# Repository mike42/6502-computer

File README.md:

# 6502 computer

This repository contains the hardware and software for my home-built 65C02-based computer. At its heart, this computer is a 1980's design, and is approximately as powerful as the Apple II. It is powered over USB, and operated via a serial connection.

It features an SD card interface, simple audio interface, and two user-selectable ROMs. One ROM contains a port of EhBASIC, which is the only proprietary component in this repository. The other ROM contains a shell, written from scratch to be free and open source, which can be used to load machine-language programs from a modern PC.

Take a look at the [hardware/](https://github.com/mike42/6502-computer/tree/main/hardware) directory for how it's made, or [rom/](https://github.com/mike42/6502-computer/tree/main/rom) for the firmware source code.

### Basic specs

- 1.8432 MHz 65C02 processor
- 32 KiB RAM
- 32 KiB ROM in two 16 KiB banks
- 65C22 VIA (general purpose I/O) chip
- 65C51N ACIA (UART) interface
- Custom PCB and 3D printed case

### Image of completed build

## Blog series

This project started out on breadboards, and I have been blogging about it as I have progressed the hardware, software, and my electronics knowlege. Posts I've written about this project include:

- [IntelliJ plugin for 6502 assembly language](https://mike42.me/blog/2021-05-intellij-plugin-for-6502-assembly-language)
- [Building a 6502 computer](https://mike42.me/blog/2021-07-building-a-6502-computer)
- [Adding a serial port to my 6502 computer](https://mike42.me/blog/2021-07-adding-a-serial-port-to-my-6502-computer)
- [Upgrades and improvements to my 6502 computer](https://mike42.me/blog/2021-08-upgrades-and-improvements-to-my-6502-computer)
- [Porting BASIC to my 6502 computer](https://mike42.me/blog/2021-09-porting-basic-to-my-6502-computer)
- [6502 computer – from breadboard to PCB](https://mike42.me/blog/2021-09-6502-computer-from-breadboard-to-pcb)
- [Re-creating the world’s worst sound card](https://mike42.me/blog/2021-10-re-creating-the-worlds-worst-sound-card)
- [Designing a 3D printed enclosure for my KiCad project in Blender](https://mike42.me/blog/2021-11-designing-a-3d-printed-enclosure-for-my-kicad-project-in-blender)
- [Implementing the XMODEM protocol for file transfer](https://mike42.me/blog/2021-12-implementing-the-xmodem-protocol-for-file-transfer)
- [Adding an SD card reader to my 6502 computer](https://mike42.me/blog/2021-12-adding-an-sd-card-reader-to-my-6502-computer)
- [Assembling my 6502 computer](https://mike42.me/blog/2012-12-assembling-my-6502-computer)
- [Rendering my 6502 computer project in Blender](https://mike42.me/blog/2022-01-rendering-my-6502-computer-project-in-blender)

## Licenses & acknowledgement

With the exception of the files noted below, this work is © 2021 Michael Billington, and is licensed under a [Creative Commons Attribution 4.0 International License](http://creativecommons.org/licenses/by/4.0/).

The design is an extension of [Ben Eater's 6502 computer tutorial](https://eater.net/6502), which is itself based on the work of the [6502.org](http://www.6502.org/) community.

### 6502 KiCad Library

The files `hardware/kicad/65xx.dcm` and `hardware/kicad/65xx.lib` are modified versions of the [6502 KiCad Library](https://github.com/Alarm-Siren/6502-kicad-library). Copyright 2018, Nicholas Parks Young. All Rights Reserved. The 6502 KiCad Library library is licensed under the GNU LGPL v2.1, which can be found in file `licenses/LGPL.txt`.

### EhBASIC

The files in `rom/basic/` are derived from EhBASIC, developed by Lee Davidson. The EhBASIC license allows for non-commerical use only. The most recent release and manual is hosted [here](https://github.com/Klaus2m5/6502_EhBASIC_V2.22), and a mirror of Lee's website can be found [here](http://retro.hansotten.nl/6502-sbc/lee-davison-web-site/).

> EhBASIC is free but not copyright free. For non commercial use there is only one
> restriction, any derivative work should include, in any binary image distributed,
> the string "Derived from EhBASIC" and in any distribution that includes human
> readable files a file that includes the above string in a human readable form
> e.g. not as a comment in an HTML file.

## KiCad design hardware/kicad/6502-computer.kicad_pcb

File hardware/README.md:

# 6502 computer hardware

This directory contains information about the hardware side of this project.

- [kicad/](https://github.com/mike42/6502-computer/tree/main/hardware/kicad) - CAD source files for schematic and PCB
- [gerber/](https://github.com/mike42/6502-computer/tree/main/hardware/gerber/) - PCB manufacturing files 
- [6502_computer_schematic.pdf](https://github.com/mike42/6502-computer/tree/main/hardware/6502_computer_schematic.pdf) - Human-readable schematic
- [case/](https://github.com/mike42/6502-computer/tree/main/hardware/case/) - STL files for 3D printed computer case.
- Parts list (below)

## Parts list for assembling PCB

This is the full list of parts which are required to fully populate the PCB for this build. I've stuck with the parts which I actually used, though many can be substituted if you check the data sheets.

### IC’s and sockets

Notes on IC's and sockets

- If you see a designator mentioned twice, one is the IC, the other is the socket.
- All sockets are optional except U9.

| Qty. | Description                    | Installed at | Product ref.                                                                         |
| ---- | ------------------------------ | ------------ | ------------------------------------------------------------------------------------ |
|   1  | 65C02S CPU                     | U1           | [WDC W65C02S6TPG-14](https://au.mouser.com/ProductDetail/955-W65C02S6TPG-14)         |
|   1  | 65C22S VIA                     | U3           | [WDC W65C22S6TPG-14](https://au.mouser.com/ProductDetail/955-W65C22S6TPG-14)         |
|   2  | DIP-40 socket                  | U1, U3       | [Mill-Max 110-99-640-41-001000](https://au.mouser.com/ProductDetail/575-199640)      |
|   1  | 65C51N ACIA                    | U6           | [WDC W65C51N6TPG-14](https://au.mouser.com/ProductDetail/955-W65C51N6TPG-14)         |
|   1  | SRAM 32k x 8                   | U8           | [Alliance AS6C62256-55PCN](https://au.mouser.com/ProductDetail/913-AS6C62256-55PCN)  |
|   2  | DIP-28 socket                  | U6, U8       | [Mill-Max 110-99-628-41-001000](https://au.mouser.com/ProductDetail/575-199628)      |
|   1  | EEPROM 32k x 8                 | U9           | [Atmel AT28C256-15PU](https://au.mouser.com/ProductDetail/556-AT28C25615PU)          |
|   1  | Low-profile DIP-28 ZIF socket  | U9           | [Aires 28-526-10](https://au.mouser.com/ProductDetail/535-28-526-10)                 |
|   1  | 74LS138 demultiplexer          | U2           | [Texas Instruments SN74LS138N](https://au.mouser.com/ProductDetail/595-SN74LS138N)   |
|   1  | DIP-16 socket                  | U2           | [Mill-Max 110-44-316-41-001000](https://au.mouser.com/ProductDetail/575-11044316)    |
|   1  | 74LS00 quad NAND gate          | U4           | [Texas Instruments SN74LS00N](https://au.mouser.com/ProductDetail/595-SN74LS00N)     |
|   1  | DIP-14 socket                  | U4           | [Mill-Max 110-44-314-41-001000](https://au.mouser.com/ProductDetail/575-11044314)    |
|   1  | 1.8432 MHz oscillator          | X1           | [CTS MXO45HS-3C-1M8432](https://au.mouser.com/ProductDetail/774-MXO45HS-3C-1.8)      |
|   1  | Oscillator socket              | X1           | [Aires 1108800](https://au.mouser.com/ProductDetail/535-1108800)                     |
|   1  | 7805 voltage regulator         | U5           | [STMicroelectronics L7805ABV](https://au.mouser.com/ProductDetail/511-L7805ABV)      |
|   1  | DS1813 reset / voltage monitor | U7           | [Maxim Integrated DS1813-5+](https://au.mouser.com/ProductDetail/700-DS1813-5%2b)    |

### Connectors

Notes on connectors:

- If you use the exact parts here, then one of the 2x20 headers needs to be snapped apart to populate 2x6 footprints at J4 and J5.
- The shunts at J3 should be installed to connect the VIA to IRQ, and the ACIA to NMI. These are labelled on the PCB.

| Qty. | Description                       | Installed at | Product ref.                                                                                           |
| ---- | --------------------------------- | ------------ | ------------------------------------------------------------------------------------------------------ |
|    2 | 2x20 male pin header              | J1, J4, J5   | [Amphenol FCI 10129381-940002BLF](https://au.mouser.com/ProductDetail/649-1012938194002BLF)            |
|    1 | Barrel jack                       | J2           | [Adafruit 373](https://au.mouser.com/ProductDetail/485-373)                                            |
|    1 | 1x6 male pin header               | J6           | [Amphenol FCI 10129378-906001BLF](https://au.mouser.com/ProductDetail/Amphenol-FCI/10129378-906001BLF) |
|    2 | SPDT switch 2.54mm lead spacing   | SW1, SW2     | [SparkFun COM-00102](https://au.mouser.com/ProductDetail/474-COM-00102)                                |
|    1 | Momentary switch                  | SW3          | [SparkFun COM-00097](https://au.mouser.com/ProductDetail/474-COM-00097)                                |
|    2 | 1x2 male pin header               | J3           | [Amphenol FCI 10129378-902001BLF](https://au.mouser.com/ProductDetail/649-1012937890201BLF)            |
|    2 | Shunt/jumper                      | J3           | [TE Connectivity 2-382811-1](https://au.mouser.com/ProductDetail/571-2-382811-1)                       |

### Basic components

| Qty. | Description                                             | Installed at                         | Product ref.                                                |
| ---- | ------------------------------------------------------- | ------------------------------------ | ----------------------------------------------------------- |
|    1 | 0.1 µF ceramic capacitor, 2.54mm lead spacing (10 pack) | C1, C2, C3, C4, C5, C6, C7, C8, C10  | [Adafruit 753](https://au.mouser.com/ProductDetail/485-753) |
|    1 | 1 µF electrolytic capacitor, 1.5mm lead spacing         | C9                                   | –                                                           |
|    1 | 1N5819 schottky diode                                   | D1                                   | –                                                           |
|    1 | 5.0 mm LED                                              | D2                                   | –                                                           |
|    3 | 3.3 kΩ resistor 1/4w                                    | R1 R2 R4                             | –                                                           |
|    1 | 1 kΩ resistor 1/4w                                      | R3                                   | –                                                           |

## Additional parts to install in case

| Qty. | Description                                              | Product ref.                                                                                                 |
| ---- | -------------------------------------------------------- | ------------------------------------------------------------------------------------------------------------ |
|    1 | 16mm Illuminated Pushbutton - Red Latching On/Off Switch | [Adafruit 1442](https://core-electronics.com.au/16mm-illuminated-pushbutton-red-latching-on-off-switch.html) |
|    1 | 330 Ω resistor 1/4w                                      | –                                                                                                            |
|    1 | Momentary Button - Panel Mount                           | [SparkFun COM-11006](https://core-electronics.com.au/momentary-button-panel-mount-black.html)                |
|    1 | Piezo Buzzer                                             | [TDK PS1240P02BT](https://core-electronics.com.au/piezo-buzzer-ps1240.html)                                  |
|    4 | M3 x 5+6mm hex standoff                                  | Generic, similar to [this](https://www.minikits.com.au/SPA-M3x5-6-B-C)                                       |
|    4 | M3 nut                                                   | [Polulu 1069](https://core-electronics.com.au/machine-hex-nut-m3-25-pack.html)                               |
|    4 | M3 x 5 mm screw                                          | [Polulu 1075](https://core-electronics.com.au/machine-screw-m3-5mm-length-phillips-25-pack.html)             |
|    1 | Heat-shrink tubing kit                                   | [Adafruit 344](https://core-electronics.com.au/heat-shrink-pack.html)                                        |
|    1 | Stranded wire                                            | –                                                                                                            |
|    1 | Du Pont connector kit                                    | –                                                                                                            |
|    1 | FTDI Cable 5V (FT232RQ-based)                            | [Sparkfun DEV-09718](https://core-electronics.com.au/ftdi-cable-5v.html)                                     |
|    1 | Adhesive rubber feet                                     | [Adafruit 550](https://core-electronics.com.au/little-rubber-bumper-feet-pack-of-4.html)                     |

### Case installation notes

First solder three pairs of wires to the underside of the PCB for adding connectors. Each wire is soldered to the PCB on one end, with a female Du Pont connector on the other end (2 x 1 housing).

- Power: Attach to pins 1 and 2 of SW1 to control DC barrel jack, or attach between Pin 4 of J6 (labelled `NC`) and Pin 1 of J5 (labelled `5V`) for power over USB.
- Reset: Connect to underside of SW3. One wire should attach to `GND`, the other to `RES`.
- Speaker: Connect to underside of J1, at pins 24 (labelled `IO2`) and pin 2 (labelled `GND`).

Next, add the corresponding connectors to the power/reset buttons and speaker.

- Power: Solder a wire to each power terminal, and terminate it to a 2x1 male Du Point connector. Solder a wire to each LED terminal, adding a resistor on the GND line, and terminating them to a 2x1 female Du Pont connector.
- Reset: Solder wire to each terminal, terminate to a 2x1 male Du Pont connector
- Speaker: Solder wire to each terminal, terminate to a 2x1 male Du Pont connector

To assemble, first check that the reset button fits (the hole is too small in the case model, and will need to be expanded). Install stand-offs, then feed the UART cable through the oval-shaped hole. Next, add the PCB, and install the power and reset buttons. After this, you can connect the UART cable, power button, and reset button to the board. The power LED connects to pin 1 and 2 of J5. The final step is to super-glue the speaker over the hole at the back of the case.

## Additional parts to install microSD

Some of the test programs in this repository expect an SD card to be connected. Any 5V-compatible microSD break-out board could be used. These exact parts will fit inside the case with the lid closed.

| Qty. | Description                                              | Product ref.                                                                                          |
| ---- | -------------------------------------------------------- | ----------------------------------------------------------------------------------------------------- |
|    1 | Level Shifting microSD Breakout                          | [Sparkfun DEV-13743](https://core-electronics.com.au/sparkfun-level-shifting-microsd-breakout.html)   |
|    1 | 1x7 male pin header                                      | Generic, similar to [this](https://au.mouser.com/ProductDetail/Amphenol-FCI/10129378-907001BLF)       |
|    1 | 1x7 female pin header                                    | [Polulu 1017](https://core-electronics.com.au/0-100-2-54-mm-female-header-1x7-pin-straight.html)      |
|    1 | 2x6 female Du Pont housing                               | [Polulu 1914](https://core-electronics.com.au/0-1-2-54mm-crimp-connector-housing-2x6-pin-5-pack.html) |
|    1 | microSD card 16 GB                                       | –                                                                                                     |

### microSD installation notes

These parts can be used to install a microSD card in the case, attaching to J4. The card sits parallel to J4.

Glue the female pin header to the side of the Du Pont housing to make an adapter. You will need 6 wires, soldered on one end, and with a female Du Pont connector on the other end:

- Pin 1 (labelled `5V`) connects to `VCC`
- Pin 2 (labelled `GND`) connects to `GND`
- Pin 5 (labelled `PA0`) connects to `DO`
- Pin 6 (labelled `PA1`) connects to `SCK`
- Pin 7 (labelled `PA2`) connects to `DI`
- Pin 8 (labelled `PA3`) connects to `CS`

Solder the male pin headers to the microSD breakout, connect the module to the adapter, and attach it to J4. Wiggle it around a bit, and add insulating tape to anything it can contact. You can then fit an SD card.

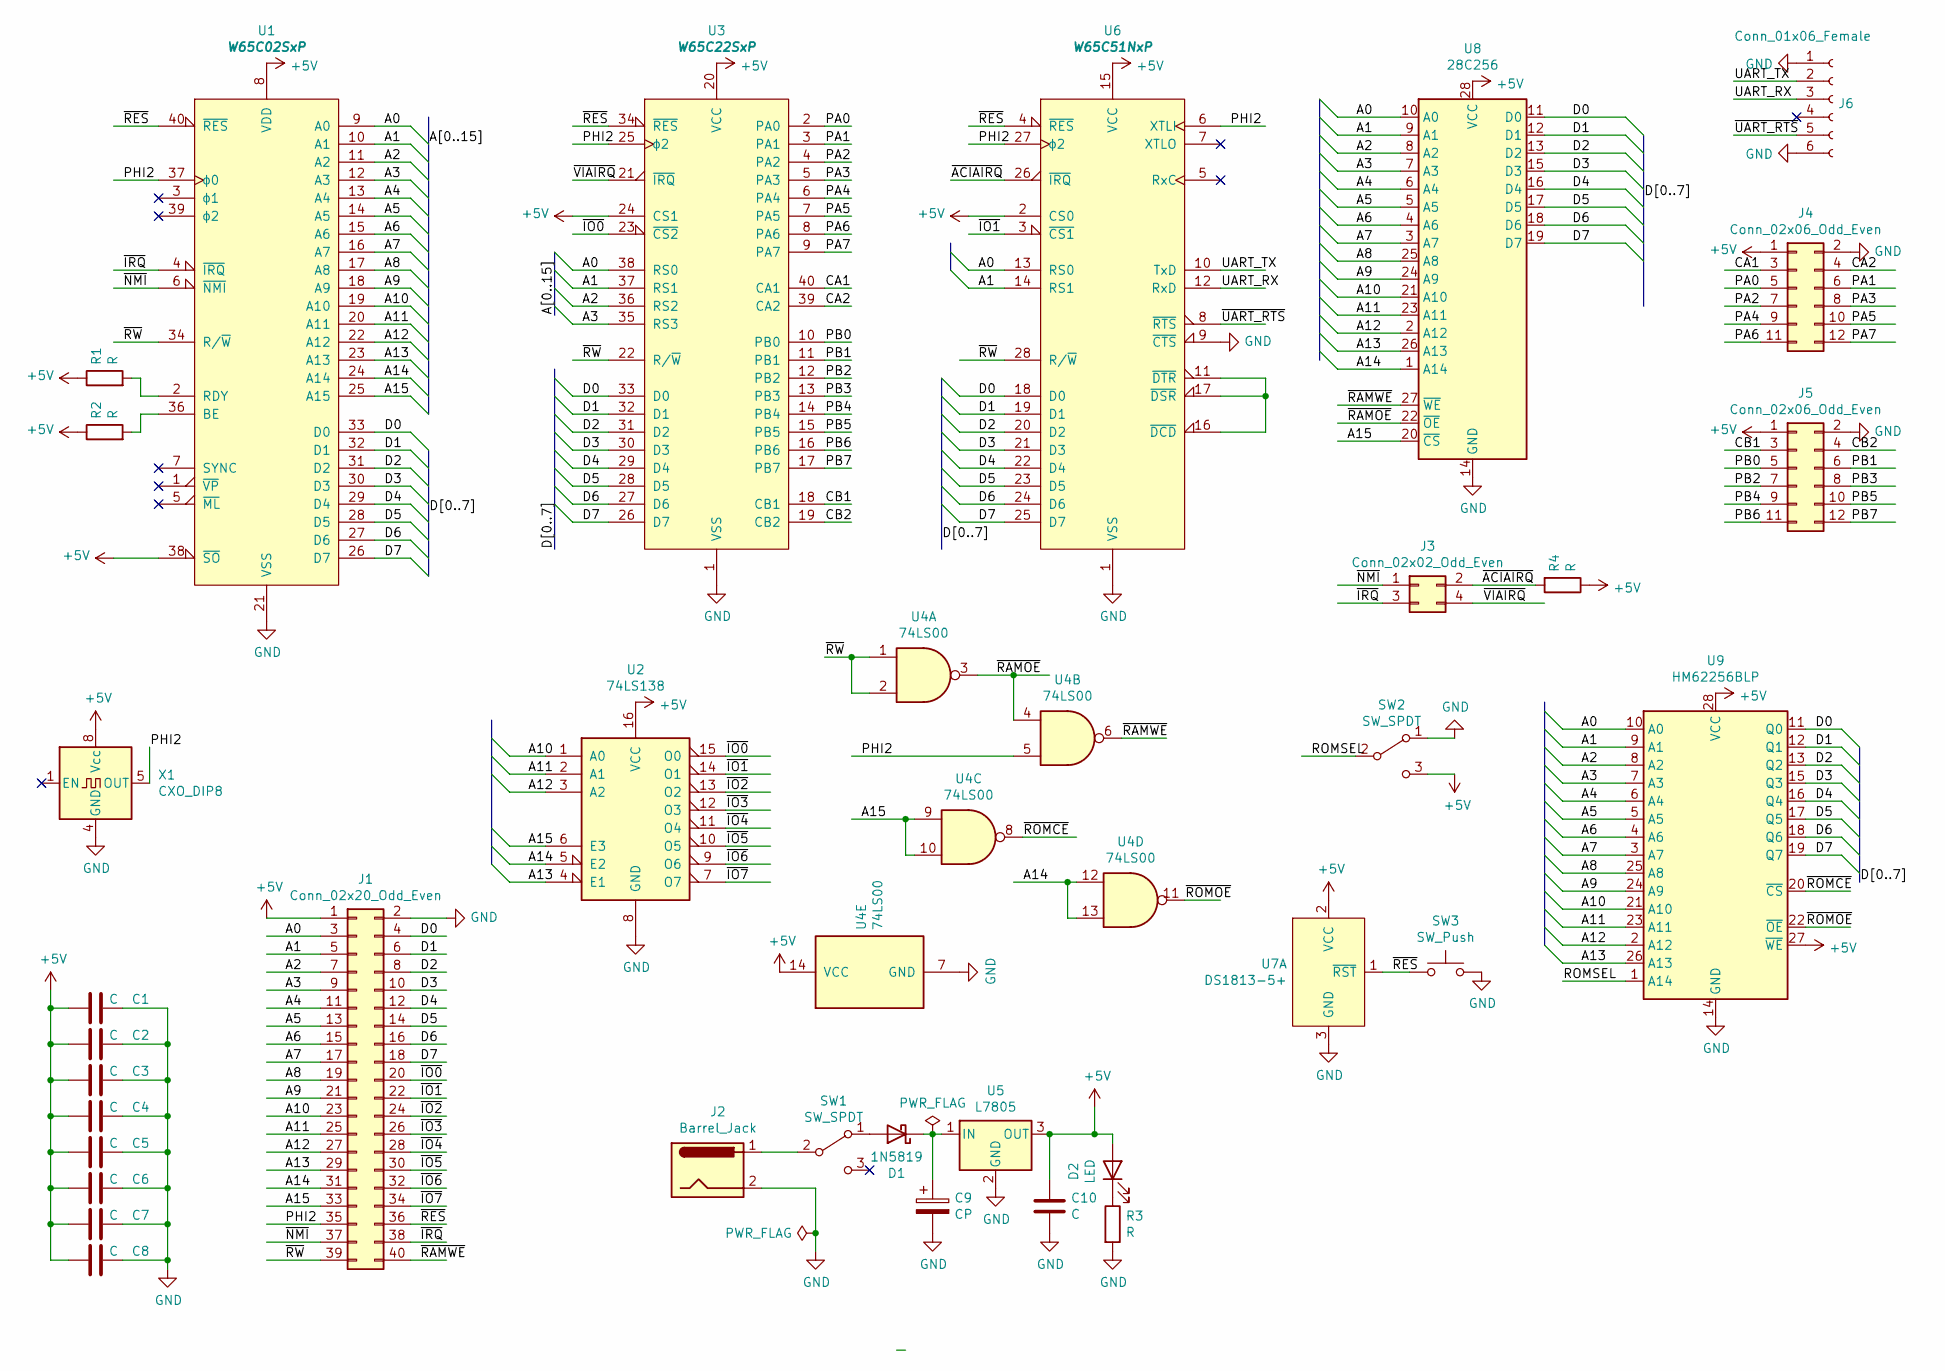
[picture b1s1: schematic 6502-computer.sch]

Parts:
C1, C2, C3, C4, C5, C6, C7, C8, C10: C; C_Disc_D5.0mm_W2.5mm_P2.50mm
C9: CP; C_Radial_D4.0mm_H7.0mm_P1.50mm
D1: 1N5819; D_DO-41_SOD81_P10.16mm_Horizontal
D2: LED; LED_D5.0mm
J1: Conn_02x20_Odd_Even; PinHeader_2x20_P2.54mm_Vertical
J2: Barrel_Jack; BarrelJack_Horizontal
J3: Conn_02x02_Odd_Even; PinHeader_2x02_P2.54mm_Vertical
J4, J5: Conn_02x06_Odd_Even; PinHeader_2x06_P2.54mm_Vertical
J6: Conn_01x06_Female; PinHeader_1x06_P2.54mm_Vertical
R1, R2, R3, R4: R; R_Axial_DIN0207_L6.3mm_D2.5mm_P10.16mm_Horizontal
SW1, SW2: SW_SPDT; SW_THT_DPDT
SW3: SW_Push; SW_Tactile_Straight_KSL0Axx1LFTR
U1: W65C02SxP; DIP-40_W15.24mm_Socket
U2: 74LS138; DIP-16_W7.62mm_Socket
U3: W65C22SxP; DIP-40_W15.24mm_Socket
U4: 74LS00; DIP-14_W7.62mm_Socket
U5: L7805; TO-220-3_Horizontal_TabDown
U6: W65C51NxP; DIP-28_W15.24mm_Socket
U7: DS1813-5+; TO-92
U8: 28C256; DIP-28_W15.24mm_Socket
U9: HM62256BLP; DIP-28_W15.24mm_Socket
X1: CXO_DIP8; Oscillator_DIP-8

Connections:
+5V: C1.2, C2.2, C3.2, C4.2, C5.2, C6.2, C7.2, C8.2, C10.1, D2.2 (A), J1.1, J4.1, J5.1, R1.1, R2.1, R4.1, SW2.3 (C), U1.8 (VDD), U1.38 (~SO), U2.16 (VCC), U3.20 (VCC), U3.24 (CS1), U4.14 (VCC), U5.3 (OUT), U6.2 (CS0), U6.15 (VCC), U7.2 (VCC), U8.28 (VCC), U9.27 (~WE), U9.28 (VCC), X1.8 (Vcc)
/A0: J1.3, U1.9 (A0), U3.38 (RS0), U6.13 (RS0), U8.10 (A0), U9.10 (A0)
/A1: J1.5, U1.10 (A1), U3.37 (RS1), U6.14 (RS1), U8.9 (A1), U9.9 (A1)
/A2: J1.7, U1.11 (A2), U3.36 (RS2), U8.8 (A2), U9.8 (A2)
/A3: J1.9, U1.12 (A3), U3.35 (RS3), U8.7 (A3), U9.7 (A3)
/A4: J1.11, U1.13 (A4), U8.6 (A4), U9.6 (A4)
/A5: J1.13, U1.14 (A5), U8.5 (A5), U9.5 (A5)
/A6: J1.15, U1.15 (A6), U8.4 (A6), U9.4 (A6)
/A7: J1.17, U1.16 (A7), U8.3 (A7), U9.3 (A7)
/A8: J1.19, U1.17 (A8), U8.25 (A8), U9.25 (A8)
/A9: J1.21, U1.18 (A9), U8.24 (A9), U9.24 (A9)
/A10: J1.23, U1.19 (A10), U2.1 (A0), U8.21 (A10), U9.21 (A10)
/A11: J1.25, U1.20 (A11), U2.2 (A1), U8.23 (A11), U9.23 (A11)
/A12: J1.27, U1.22 (A12), U2.3 (A2), U8.2 (A12), U9.2 (A12)
/A13: J1.29, U1.23 (A13), U2.4 (E1), U8.26 (A13), U9.26 (A13)
/A14: J1.31, U1.24 (A14), U2.5 (E2), U4.12, U4.13, U8.1 (A14)
/A15: J1.33, U1.25 (A15), U2.6 (E3), U4.9, U4.10, U8.20 (~CS)
/CA1: J4.3, U3.40 (CA1)
/CA2: J4.4, U3.39 (CA2)
/CB1: J5.3, U3.18 (CB1)
/CB2: J5.4, U3.19 (CB2)
/D0: J1.4, U1.33 (D0), U3.33 (D0), U6.18 (D0), U8.11 (D0), U9.11 (Q0)
/D1: J1.6, U1.32 (D1), U3.32 (D1), U6.19 (D1), U8.12 (D1), U9.12 (Q1)
/D2: J1.8, U1.31 (D2), U3.31 (D2), U6.20 (D2), U8.13 (D2), U9.13 (Q2)
/D3: J1.10, U1.30 (D3), U3.30 (D3), U6.21 (D3), U8.15 (D3), U9.15 (Q3)
/D4: J1.12, U1.29 (D4), U3.29 (D4), U6.22 (D4), U8.16 (D4), U9.16 (Q4)
/D5: J1.14, U1.28 (D5), U3.28 (D5), U6.23 (D5), U8.17 (D5), U9.17 (Q5)
/D6: J1.16, U1.27 (D6), U3.27 (D6), U6.24 (D6), U8.18 (D6), U9.18 (Q6)
/D7: J1.18, U1.26 (D7), U3.26 (D7), U6.25 (D7), U8.19 (D7), U9.19 (Q7)
/PA0: J4.5, U3.2 (PA0)
/PA1: J4.6, U3.3 (PA1)
/PA2: J4.7, U3.4 (PA2)
/PA3: J4.8, U3.5 (PA3)
/PA4: J4.9, U3.6 (PA4)
/PA5: J4.10, U3.7 (PA5)
/PA6: J4.11, U3.8 (PA6)
/PA7: J4.12, U3.9 (PA7)
/PB0: J5.5, U3.10 (PB0)
/PB1: J5.6, U3.11 (PB1)
/PB2: J5.7, U3.12 (PB2)
/PB3: J5.8, U3.13 (PB3)
/PB4: J5.9, U3.14 (PB4)
/PB5: J5.10, U3.15 (PB5)
/PB6: J5.11, U3.16 (PB6)
/PB7: J5.12, U3.17 (PB7)
/PHI2: J1.35, U1.37 (ϕ0), U3.25 (ϕ2), U4.5, U6.6 (XTLI), U6.27 (ϕ2), X1.5 (OUT)
/ROMSEL: SW2.2 (B), U9.1 (A14)
/UART_RX: J6.3, U6.12 (RxD)
/UART_TX: J6.2, U6.10 (TxD)
/~ACIAIRQ: J3.2, R4.2, U6.26 (~IRQ)
/~IO0: J1.20, U2.15 (O0), U3.23 (~CS2)
/~IO1: J1.22, U2.14 (O1), U6.3 (~CS1)
/~IO2: J1.24, U2.13 (O2)
/~IO3: J1.26, U2.12 (O3)
/~IO4: J1.28, U2.11 (O4)
/~IO5: J1.30, U2.10 (O5)
/~IO6: J1.32, U2.9 (O6)
/~IO7: J1.34, U2.7 (O7)
/~IRQ: J1.38, J3.3, U1.4 (~IRQ)
/~NMI: J1.37, J3.1, U1.6 (~NMI)
/~RAMOE: U4.3, U4.4, U8.22 (~OE)
/~RAMWE: J1.40, U4.6, U8.27 (~WE)
/~RES: J1.36, SW3.1, U1.40 (~RES), U3.34 (~RES), U6.4 (~RES), U7.1 (~RST)
/~ROMCE: U4.8, U9.20 (~CS)
/~ROMOE: U4.11, U9.22 (~OE)
/~RW: J1.39, U1.34 (R/~W), U3.22 (R/~W), U4.1, U4.2, U6.28 (R/~W)
/~UART_RTS: J6.5, U6.8 (~RTS)
/~VIAIRQ: J3.4, U3.21 (~IRQ)
GND: C1.1, C2.1, C3.1, C4.1, C5.1, C6.1, C7.1, C8.1, C9.2, C10.2, J1.2, J2.2, J4.2, J5.2, J6.1, J6.6, R3.2, SW2.1 (A), SW3.2, U1.21 (VSS), U2.8 (GND), U3.1 (VSS), U4.7 (GND), U5.2 (GND), U6.1 (VSS), U6.9 (~CTS), U7.3 (GND), U8.14 (GND), U9.14 (GND), X1.4 (GND); also elsewhere on the board
unnamed: C9.1, D1.1 (K), U5.1 (IN)
unnamed: D1.2 (A), SW1.1 (A)
unnamed: D2.1 (K), R3.1
unnamed: J2.1, SW1.2 (B)
unnamed: R1.2, U1.2 (RDY)
unnamed: R2.2, U1.36 (BE)
unnamed: U6.11 (~DTR), U6.16 (~DCD), U6.17 (~DSR)

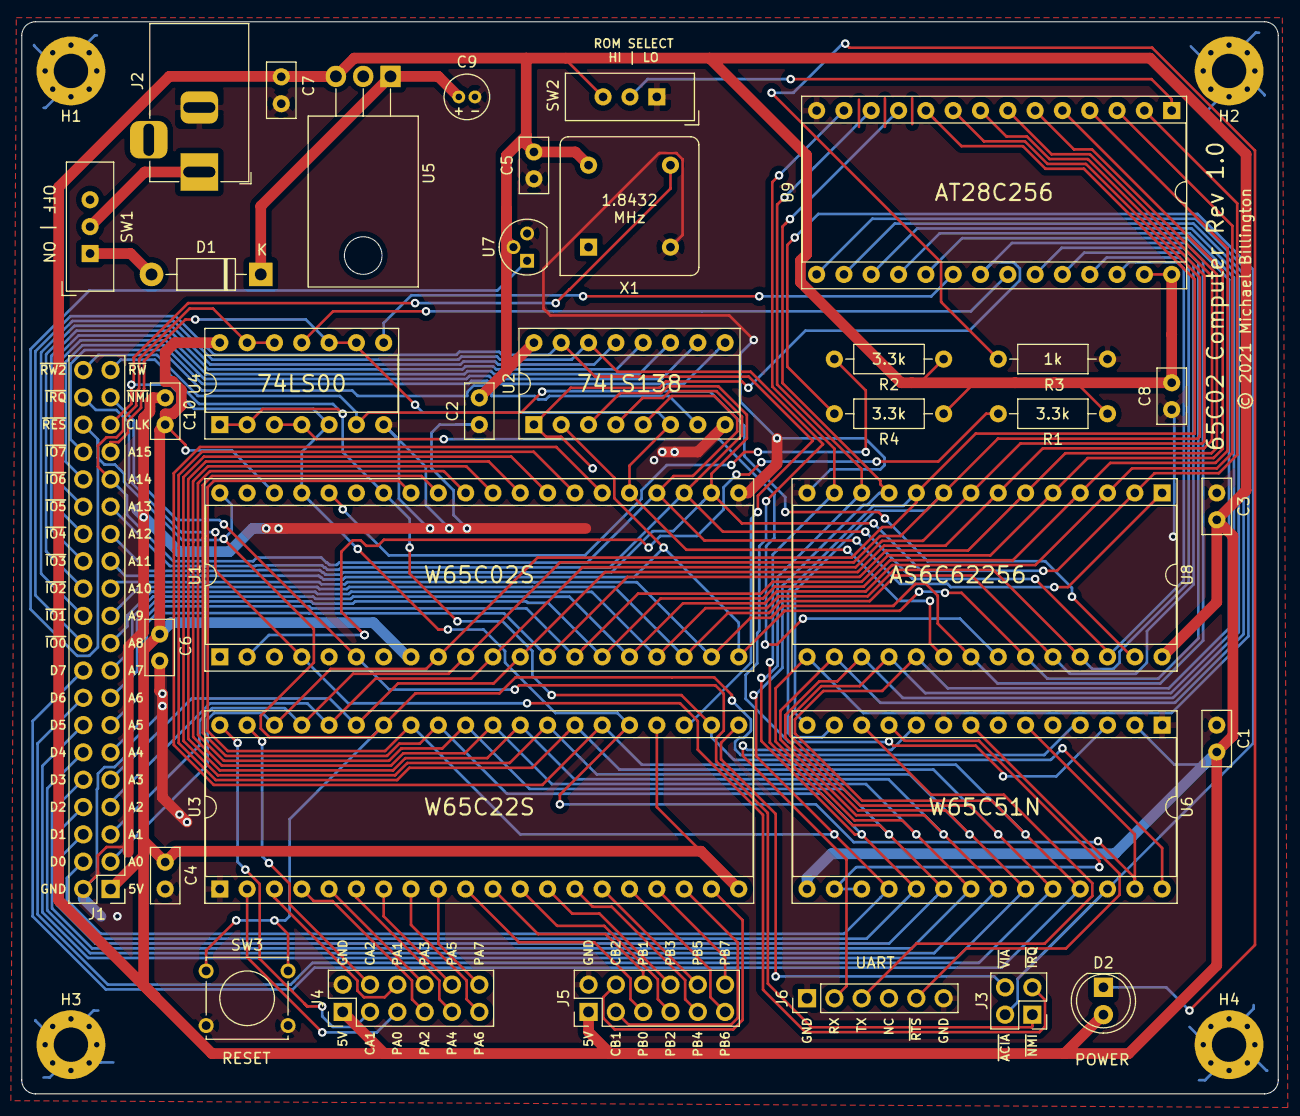
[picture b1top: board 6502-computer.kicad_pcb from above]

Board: 2 copper layers, 116.8 x 99.7 mm, 39 parts (0 on the bottom side), 76 nets.

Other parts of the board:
H1, H2, H3, H4: MountingHole_3.2mm_M3_Pad_Via

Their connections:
GND: H1.1, H2.1, H3.1, H4.1; also elsewhere on the board

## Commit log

2021-08-15 Initial commit, schematic + gerbers
2021-08-15 add LICENSE.md
2021-08-15 initial commit github.com/Klaus2m5/6502_EhBASIC_V2.22 patched files + copyright notice only
2021-08-15 modify for ca65 assembly to 16KiB ROM, loaded from $c000, 65c51 ACIA, 65c02 CPU target
2021-08-22 add component values
2021-08-22 add PDF schematic, parts list
2021-08-24 update assembly files, add firmware for high ROM.
2021-08-28 add abiltiy to run named commands from ROM
2021-08-31 minor README fix
2021-09-05 add blank rx command, start of irq tests
2021-09-05 add irq controller test code
2021-09-19 progress adding XMODEM transfers
2021-09-19 fixes to XMODEM recieve (128 bytes only)
2021-09-21 improve timing
2021-09-29 restructure for custom programs
2021-09-29 more changes to support programs outside ROM
2021-10-01 split programs out of boot ROM directory
2021-10-03 firmware fixes, first attempt at SPI/SD card interface
2021-10-03 second attempt at SPI/SD card interface
2021-10-03 fix code - SD initialization works
2021-10-04 update SD card test code, add new linker config
2021-10-09 add case STL files
2021-10-11 add PCB diagram
2021-10-25 fix SD card read block to RAM, was saving in reverse
2021-10-31 change SD pinout
2021-11-08 add case install notes
2021-12-20 add image of finished project
2021-12-20 shrink image
2021-12-20 expand README
2021-12-30 Add new blog post
2022-01-13 Add new blog post.
2022-01-19 add test program for interfacing with NXP SC16C752B
